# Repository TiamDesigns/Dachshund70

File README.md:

# Dachshund70

A tri-mode 60% keyboard I'm designing from scratch: the PCBs, the switch plate, the firmware, the config protocol, the driver and the configurator app. It runs over USB, Bluetooth LE and its own 2.4 GHz dongle, all on the nRF52840.

It was called the Dachshund60F until November 2026; older notes, PRs and the 26 October project review still use that name.

No boards have been made yet. All three PCBs are designed and the firmware is built and tested on a PC, so the next step is ordering them and bringing them up.

## Why I'm building this

I'm using this project to do two things at once:

1. **Explore hardware design with AI.** I want to see how far I can push an AI-assisted workflow on a real product: schematics, PCB layout, firmware, tooling and docs. I make the decisions and review everything, and Claude Code does a lot of the legwork. This repo is the record of how that went.
2. **Learn high-speed peripherals properly.** A keyboard looks simple, but doing it right covers USB device design, Bluetooth LE, a proprietary 2.4 GHz radio link, SPI and I2C displays, addressable LEDs, flash storage and power management. I want to understand each one well enough to design it, not just copy it.

And at the end of it I want a keyboard I actually enjoy using every day.

## Project goals

### Hardware

- Design all the boards myself in KiCad: the mainboard, a USB-C daughterboard and the dongle, plus an FR4 switch plate.
- Use a pre-certified nRF52840 module (Raytac MDBT50Q-P1MV2) and get the antenna keep-out, power and USB right the first time.
- Make it nice to type on: hot-swap switches, screw-in stabilisers, a gasket-mounted plate, and a horizontal roller encoder that turns like a mouse wheel.
- Run from USB or a single LiPo cell, with proper charging and a power path so it still works with the battery switched off.
- Measure everything when the boards arrive: rails, current draw in every state, scan rate, latency and radio range. The plan is in [docs/bringup-test-plan.md](docs/bringup-test-plan.md).

### Firmware

- Write my own firmware on Zephyr / nRF Connect SDK, not a fork of QMK or ZMK.
- Keep the keymap logic in plain C with no hardware in it, so it runs as unit tests on a PC.
- Be a complete USB keyboard: NKRO with boot-protocol fallback for BIOS and KVMs, media keys, lock LEDs, and suspend and remote wakeup.
- Support the advanced stuff: tap-hold, combos, tap dance, macros, key overrides, Caps Word, Auto Shift, Leader, mouse keys and the encoder.
- Never crash or corrupt flash on a bad packet. Every index and length from the host is checked, and the parser is fuzzed.

### Wireless

- Bluetooth LE HID with several host profiles and a switch key.
- A 2.4 GHz dongle on a second nRF52840 with low latency, polling at 1000 Hz (the limit for full-speed USB).
- Battery reporting, idle sleep and wake on key press.

### Driver and app

- No kernel driver. The board shows up as a normal HID keyboard plus one vendor-defined HID interface for configuration, so it works anywhere with nothing to install.
- A TypeScript host library (the "driver") that talks to that interface over WebHID in the browser or node-hid on the desktop.
- **Doghouse**, the configurator: keymap editing, advanced keys, macros, settings and firmware updates. It runs in Chrome or Edge, or as a desktop app for Windows, macOS and Linux that updates itself. It's in warm earth tones and dog-themed, because the boards are named after dogs.

### Doing it properly

- One protocol definition (`protocol/protocol.yaml`), with the C and TypeScript code generated from it.
- Versioned, CRC-checked, wear-levelled settings in flash, with migrations.
- CI that runs the unit tests, the host-library tests, the app build, protocol fuzzing, and debug and release firmware builds on every PR.
- Write down what changed and what's been tested in [PROGRESS.md](PROGRESS.md).

## The board

| | |
| --- | --- |
| MCU | nRF52840 (Raytac MDBT50Q-P1MV2 module) |
| Layout | 60% with an F-row, 80 switch positions, split or 6.25u spacebar |
| Matrix | 6 × 15, COL2ROW, diodes on every switch |
| Switches | Kailh hot-swap sockets (3 soldered positions on the spacebar row) |
| Encoder | Bourns PEC12R-2230F-S0024: shaft parallel to the board, 24 detents, push switch, 30 mm shaft, used as a 2u roller. On its own module board, cabled to the mainboard |
| Lighting | 6 × SK6812MINI-E indicators: layer, a 4-step battery gauge, and Caps Lock. No per-key RGB |
| Display | Sharp LS027B7DH01 2.7" memory LCD (240 × 400 on end), plugged into the mainboard's J4 with its 5 V boost on board; OLED and e-paper overlays still build for wired adapters |
| Power | USB-C on a daughterboard, 1S LiPo on JST-PH, MCP73831 charger with a load-sharing power path |
| Connectivity | USB, Bluetooth LE, 2.4 GHz dongle |
| Bootloader | Adafruit nRF52 UF2 bootloader: double-tap reset and drag a `.uf2` onto the drive |
| USB IDs | pid.codes test PIDs 1209:0001 (keyboard), 1209:0002 (dongle), 1209:0003 (bootloader) |

## Where it's at

The firmware follows the build order in [SPEC.md](SPEC.md): wired first, then wireless.

| Phase | What it covers | Status |
| --- | --- | --- |
| 1 | Scaffold: monorepo, CI, Zephyr app | Done |
| 2 | Board bring-up, USB enumeration, UF2 bootloader | Done |
| 3 | Matrix scan, debounce, keycodes, layers, tap-hold | Done |
| 4 | Full USB HID: NKRO, media keys, lock LEDs, sleep and wake | Done |
| 5 | Config protocol v1 over a vendor HID interface | Done |
| 6 | Saving settings to flash | Done |
| 7 | Host library (WebHID and node-hid) | Done |
| 8 | Doghouse on real boards | Done |
| 9 | Advanced keys, macros and the encoder | Done |
| 10 | Indicator colours and global settings | Done |
| 11 | In-app firmware updates | Done |
| 12 | Bluetooth LE | Done |
| 13 | Power management, battery and input delay | Done |
| 14 | 2.4 GHz dongle firmware | Done |
| 15 | Desktop app packaging and auto-update | Done |

"Done" means built and tested on a PC and in CI. None of it has run on a real board yet, because there isn't one.

## Repo layout

| Folder | What's in it |
| --- | --- |
| `hardware/` | KiCad 10 projects: mainboard, USB-C daughterboard, dongle and plate, STEP exports, and the case (`hardware/case/`, CadQuery) |
| `boards/Dachshund70/` | Pin map, keyboard definition, Zephyr board files and the UF2 bootloader board |
| `boards/Pup/` | A one-key test board: the keyboard firmware on Nordic's nRF52840 Dongle, for trying the wireless outputs before the PCB exists |
| `firmware/` | The keyboard firmware. `firmware/core/` is the hardware-free keymap engine and its tests |
| `dongle/` | 2.4 GHz receiver firmware (see `dongle/README.md` to flash and pair it) |
| `protocol/` | `protocol.yaml` and the code generator |
| `host-lib/` | The TypeScript host library, mock board and tests |
| `app/` | Doghouse, the configurator (Svelte 5 + Vite), and its desktop app in `app/src-tauri/` (Tauri) |
| `docs/` | Bring-up and test plan, and my design decisions |

## Trying it out

You don't need a board to play with most of it.

**Doghouse with demo boards**

```sh
cd app
npm install
npm run dev
```

Then open http://localhost:5173/?demo. To use a real board, open http://localhost:5173 in Chrome or Edge and click **Connect a board…**.

**Tests**

```sh
# keymap engine and protocol (C, runs on the PC)
cmake -S firmware/core -B firmware/core/build
cmake --build firmware/core/build
ctest --test-dir firmware/core/build --output-on-failure

# host library
cd host-lib && npm ci && npm test
```

**Firmware**

From an nRF Connect SDK v3.4.1 shell, in the repo root:

```sh
west build -p -b dachshund70/nrf52840 -d build/firmware firmware -- -DBOARD_ROOT="$PWD"
```

[CLAUDE.md](CLAUDE.md) has every command, including release builds, display panels, the bootloader and flashing.

## Docs

- [SPEC.md](SPEC.md): scope and build order
- [PROGRESS.md](PROGRESS.md): what's done, what's tested, known issues
- [docs/design-decisions.md](docs/design-decisions.md): the decisions I made along the way and what I've learnt
- [docs/bringup-test-plan.md](docs/bringup-test-plan.md): how each board gets flashed, tested and measured
- [protocol/README.md](protocol/README.md): the config protocol
- [SCHEDULED_TASKS.md](SCHEDULED_TASKS.md): open tasks

## Licence and disclaimer

This is open source and open hardware. You're free to copy it, change it, build it and sell it.

- **Code** (firmware, host library, Doghouse, protocol, scripts) is under the [MIT License](LICENSE).
- **Hardware** (everything in `hardware/`: the three PCBs and the plate) is under the [CERN Open Hardware Licence v2, Permissive](hardware/LICENSE) (CERN-OHL-P-2.0).
- **Third-party files** keep their own licences. The keyswitch footprints and 3D models are CC-BY-SA-4.0 (see `hardware/Dachshund70/lib/README.md`), and the bootloader build fetches Adafruit's MIT-licensed source.

Both licences are permissive. You can make your own boards, fork the firmware, put it in a product, or sell keyboards based on it, commercially or not. All I ask, and all the licences require, is that you keep the copyright and licence notices with what you copy.

Please read this before you build one:

- **No warranty.** This is a personal learning project, provided as is. At the time of writing no board has been manufactured or tested, so the designs may have mistakes. Check them yourself before ordering.
- **Lithium batteries can be dangerous.** The board charges a LiPo cell. Use a cell with its own protection circuit, check the connector polarity (JST-PH polarity isn't standard between vendors), and don't leave it charging unattended until you've tested your build.
- **USB IDs: change them before you give a board to anyone.** I've chosen not to register USB IDs for this project, because my board only lives on my desk. The firmware uses pid.codes *test* PIDs (1209:0001, 0002 and 0003), which anyone may use for in-house testing but which **must not** be used on a device that's given away, sold or manufactured. Every board using them looks identical to the OS, and to every other project that uses the same test IDs. If your boards will leave your hands, get your own VID/PID (a free PID from [pid.codes](https://pid.codes/howto/) for open-source hardware, or a VID from the USB-IF) and change them in `firmware/Kconfig`, the dongle and bootloader configs, and `boards/Dachshund70/board.json`.
- **Certification.** The radio module is pre-certified, but a finished product may still need its own testing (FCC, CE and so on) before you sell it. That's on you.

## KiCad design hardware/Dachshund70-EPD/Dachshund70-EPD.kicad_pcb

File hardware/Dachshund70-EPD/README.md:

# Dachshund70 e-paper adapter

Rev 1.5 (2026-11-25), checked against Good Display's GDEY027T91-FT11 specification (rev 1.0, 2024-11-06). Joins the wired mainboard's screen connector (`hardware/Dachshund70-Wired/`, J4) to Good
Display's [GDEY027T91-FT11](https://www.good-display.com/product/611.html): a 2.7" e-paper (SSD1680, 264 × 176,
70.42 × 45.8 × 2.1 mm, picture 57.29 × 38.19 mm) with an FT6336U capacitive touch panel and a 4-LED front light. It
fits the right-hand column between the knob and the arrow keys with the picture as wide as the knob. (Rev 1.0 was
for the 3.7" GDEY037T03-FT21, rev 1.1 for the 2.9" GDEY029T94-FT01; both were too big for the case.) The panel comes
bare on three FPCs, so this board carries the e-paper's booster circuit and the front light's driver. KiCad 10,
2 layers, 44 × 30 mm (narrower than the panel, to sit behind it), every part on the top. ERC 0; DRC clean
(0 violations, 0 unconnected, schematic parity clean). Not ordered, not tested.

## Connectors

J2 (e-paper), J3 (touch) and J4 (front light) are Hirose FH34SRJ dual-contact sockets (contacts top and bottom, 1 mm
high, LCSC C324726 / C224194), so a panel tail works either way up after it folds under the panel. Their footprints
are in `lib/Dachshund70-EPD.pretty` (made from LCSC's land patterns by `tools/mk_fh34.py`). They face the top edge
(y = 100): J4 (front light) at x 105.4, J2 (e-paper) at 122, J3 (touch) at 138.6. In the case the board sits under
the panel, component side up, turned 180° from this view; the case model was used to set each socket's pin order so
that each folded tail's pin 1 lands on the panel's pin 1. So J2 and J3 are numbered in reverse of the panel (socket
pin k = panel pin 25 − k, and 7 − k); J4 matches the panel. J1 (to the mainboard) is a bottom-contact Hirose FH12-16S
facing the bottom edge (y = 130) at x 122.

| Ref | To | Pins |
|---|---|---|
| J1 | mainboard J4, FH12-16S (16-way 0.5 mm FFC) | 1-2 +3V3, 3 GND, 4 TP_RST, 5 GND, 6 TP_INT, 7 TP_SCL, 8 TP_SDA, 9 FL_PWM, 10 not used (TP_EN), 11 EPD_BUSY, 12 EPD_RST, 13 EPD_DC, 14 EPD_MOSI, 15 EPD_SCK, 16 EPD_CS |
| J2 | e-paper FPC, FH34SRJ-24S | panel pins (socket pin = 25 − panel pin), per the spec (SSD1680): 2 GDR, 3 RESE, 5 VSH2, 8 BS1 (to GND: 4-wire SPI), 9 BUSY, 10 RES#, 11 D/C#, 12 CS#, 13 SCL, 14 SDA, 15 VDDIO, 16 VCI, 17 VSS, 18 VDD, 20 VSH1, 21 VGH, 22 VSL, 23 VGL, 24 VCOM; 1, 4, 6, 7 (TSCL/TSDA, no external sensor) and 19 (VPP, for test) not connected |
| J3 | touch FPC, FH34SRJ-6S | panel pins (socket pin = 7 − panel pin), per the spec: 1 GND, 2 INT, 3 RST, 4 VDD (+3V3), 5 SCL, 6 SDA (pull-ups are on the mainboard) |
| J4 | front-light FPC, FH34SRJ-6S | per the spec: 1-2 A(+) (FL_VOUT), 3-4 NC, 5-6 K(-) (FL_FB) |

## Circuits

- **E-paper booster**, as the spec's reference circuit: L1 47 µH (3015, 430 mA), Q1 Si1308EDL switched by GDR (R4 1M
  pull-down) with R1 2.2 Ω current sense on RESE, D3 to VGH, and the C10 (4.7 µF 25 V) / D1 / D2 charge pump to VGL
  (MBR0530 Schottkys), with 1 µF (50 V) on VSH2, VDD, VSH1, VGH, VSL, VGL, VCOM and VCI/VDDIO, and C11 4.7 µF on the
  3.3 V input.
- **Front light**: the FT11's four LEDs are in series (up to 12 V, 15 mA), so U1 (TPS61040, LCSC C7722) boosts 3.3 V
  and regulates their current: L2 10 µH, D4 MBR0530, C13 1 µF 50 V on the output, R2 82 Ω from the LEDs' cathode to
  ground (1.233 V / 82 Ω = 15 mA). FL_PWM (GPIO40) drives the TPS61040's EN to dim it with PWM (keep it under about
  1 kHz); R3 (100k) holds it off at reset.
- **Touch**: straight through, with C12 (100 nF) at J3.

## Layout

Two layers with ground pours on both, every ground pad joined solid (`Dachshund70-EPD.kicad_dru`), and one via per
cut-off pour area. Routed with the mainboard's grid router (`tools/`: placement in `epd_place.json`, net order in
`plan.json`, `epost.sh` for prune, pour, stitch and DRC).

## Open checks

- **Front-light open circuit.** The TPS61040 has no over-voltage limit: with the LEDs unplugged its output can rise
  to the switch's 28 V rating. C13 is 50 V; don't run the light without the panel attached.
- **FPC tails.** The case model sets the sockets' pin order and sides; the 6-pin tails' exact positions in Good
  Display's drawing are approximate, so check the fit on the first panel.
- **FPC tail lengths.** The 24-pin tail is 12.5 mm wide and about 30 mm long, the touch tail about 36 mm, both leaving the
  panel's bottom end; check they reach J2 and J3 when folded behind the panel in the case model.
- **FFC to the mainboard.** 16-way, 0.5 mm, 60 mm, opposite-side contacts (type B), for the case's two-fold route
  (pin 1 meets pin 1).
- **Mounting.** No holes: the case decides how the board and panel are held.

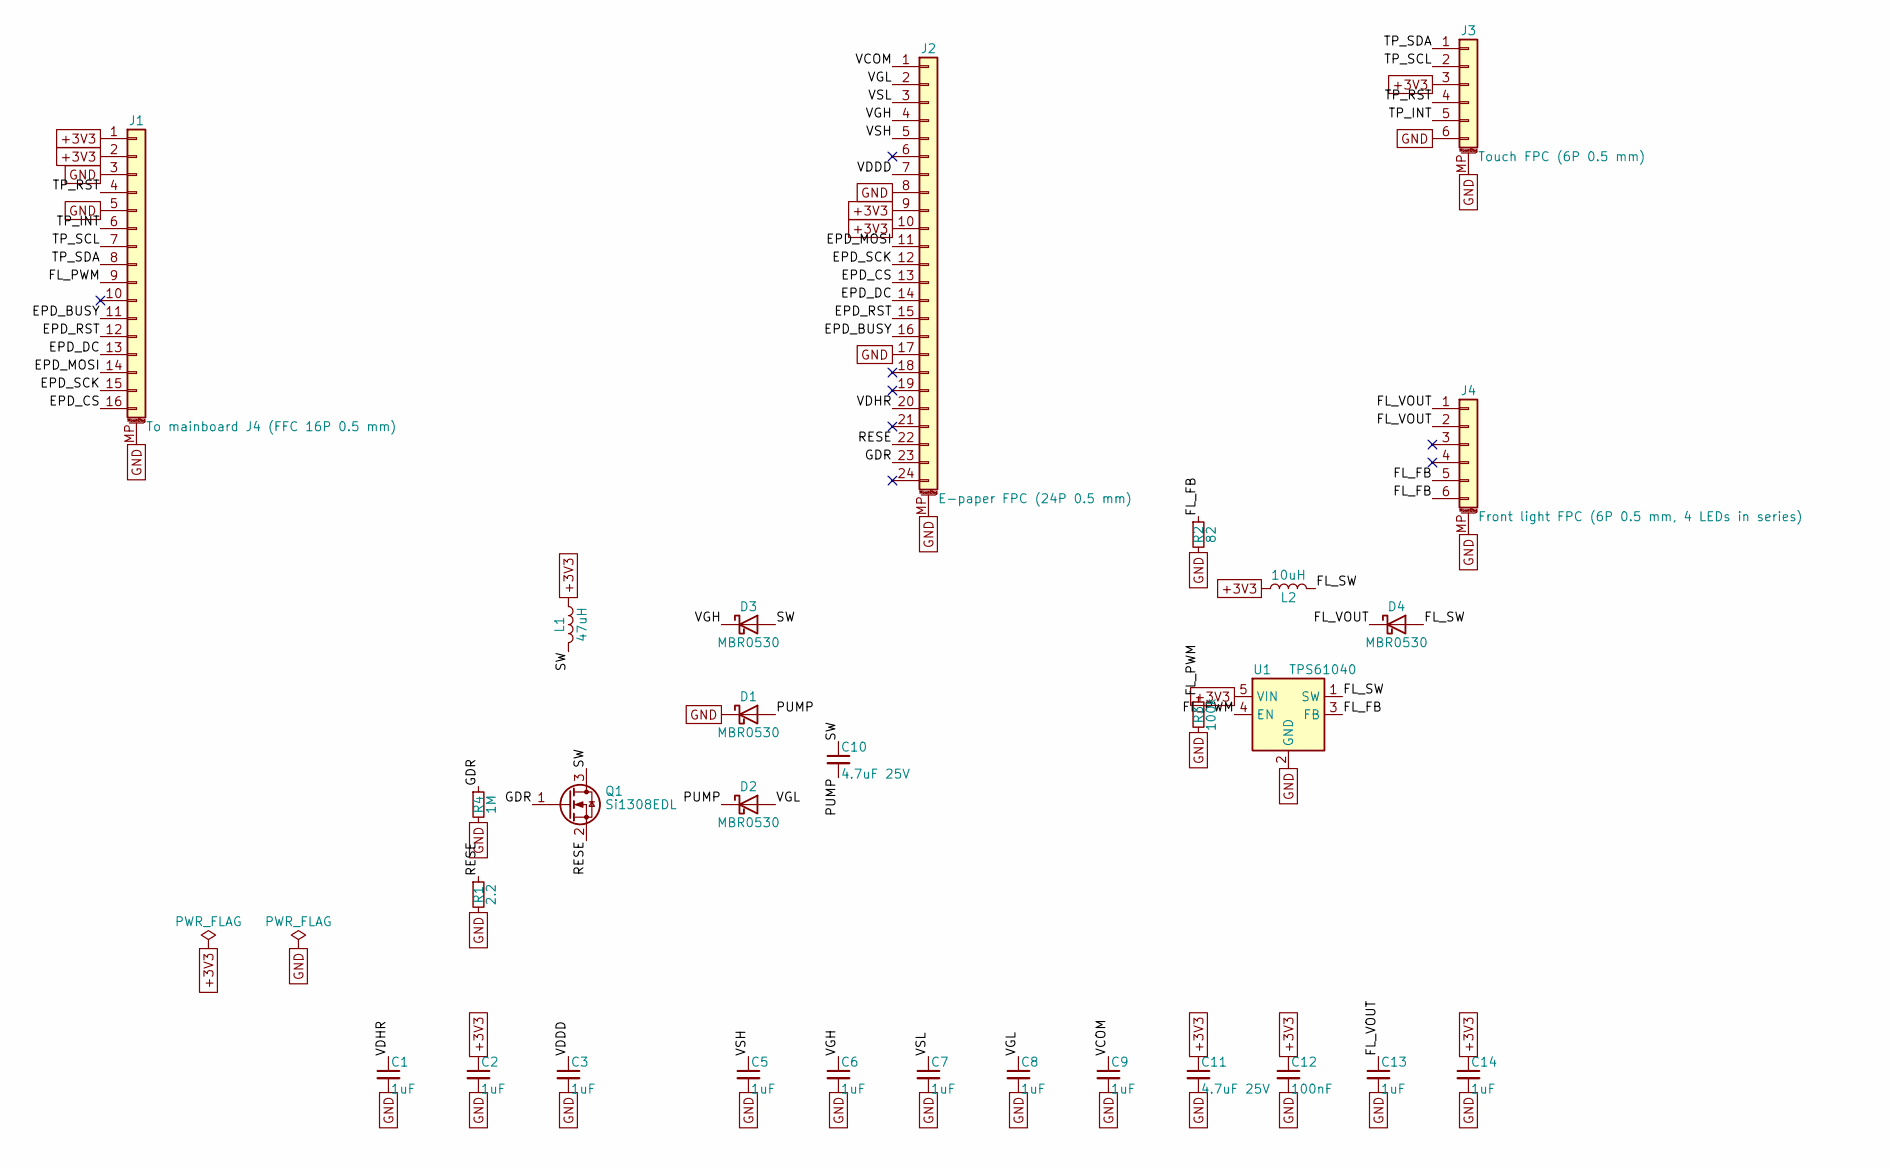
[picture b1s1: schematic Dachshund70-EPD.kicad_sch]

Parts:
C1, C2, C3, C5, C6, C7, C8, C9, C13, C14: 1uF; C_0603_1608Metric; MPN CL10A105KB8NNNC; LCSC C15849
C10, C11: 4.7uF 25V; C_0805_2012Metric; MPN CL21A475KAQNNNE; LCSC C1779
C12: 100nF; C_0603_1608Metric; MPN CC0603KRX7R9BB104; LCSC C14663
D1, D2, D3, D4: MBR0530; D_SOD-123; MPN MBR0530T1G; LCSC C82046
J1: To mainboard J4 (FFC 16P 0.5 mm); Hirose_FH12-16S-0.5SH_1x16-1MP_P0.50mm_Horizontal; MPN Hirose FH12-16S-0.5SH(55); LCSC C596731
J2: E-paper FPC (24P 0.5 mm); Hirose_FH34SRJ-24S-0.5SH_1x24-1MP_P0.50mm_Horizontal; MPN Hirose FH34SRJ-24S-0.5SH(50) (dual cont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; LCSC C324726
J3: Touch FPC (6P 0.5 mm); Hirose_FH34SRJ-6S-0.5SH_1x06-1MP_P0.50mm_Horizontal; MPN Hirose FH34SRJ-6S-0.5SH(50) (dual conta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; LCSC C224194
J4: Front light FPC (6P 0.5 mm, 4 LEDs in series); Hirose_FH34SRJ-6S-0.5SH_1x06-1MP_P0.50mm_Horizontal; MPN Hirose FH34SRJ-6S-0.5SH(50) (dual conta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; LCSC C224194
L1: 47uH; L_Changjiang_FNR3015S; MPN FNR3015S470MT (47uH 430mA, 3015); LCSC C167766
L2: 10uH; L_1008_2520Metric; MPN FHD252012S-100MT (10uH 1A, 2520); LCSC C602018
Q1: Si1308EDL; SOT-323_SC-70; MPN SI1308EDL-T1-GE3; LCSC C469327
R1: 2.2; R_0603_1608Metric; MPN 0603WAF220KT5E; LCSC C22939
R2: 82; R_0603_1608Metric; MPN 0603WAF820JT5E; LCSC C23255
R3: 100k; R_0603_1608Metric; MPN 0603WAF1003T5E; LCSC C25803
R4: 1M; R_0603_1608Metric; MPN 0603WAF1004T5E; LCSC C22935
U1: TPS61040; SOT-23-5; MPN TPS61040DBVR; LCSC C7722

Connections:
+3V3: C2.1, C11.1, C12.1, C14.1, J1.1, J1.2, J2.9, J2.10, J3.3, L1.1, L2.1, U1.5 (VIN)
/EPD_BUSY: J1.11, J2.16
/EPD_CS: J1.16, J2.13
/EPD_DC: J1.13, J2.14
/EPD_MOSI: J1.14, J2.11
/EPD_RST: J1.12, J2.15
/EPD_SCK: J1.15, J2.12
/FL_FB: J4.5, J4.6, R2.1, U1.3 (FB)
/FL_PWM: J1.9, R3.1, U1.4 (EN)
/FL_SW: D4.2 (A), L2.2, U1.1 (SW)
/FL_VOUT: C13.1, D4.1 (K), J4.1, J4.2
/GDR: J2.23, Q1.1 (G), R4.1
/PUMP: C10.2, D1.2 (A), D2.1 (K)
/RESE: J2.22, Q1.2 (S), R1.1
/SW: C10.1, D3.2 (A), L1.2, Q1.3 (D)
/TP_INT: J1.6, J3.5
/TP_RST: J1.4, J3.4
/TP_SCL: J1.7, J3.2
/TP_SDA: J1.8, J3.1
/VCOM: C9.1, J2.1
/VDDD: C3.1, J2.7
/VDHR: C1.1, J2.20
/VGH: C6.1, D3.1 (K), J2.4
/VGL: C8.1, D2.2 (A), J2.2
/VSH: C5.1, J2.5
/VSL: C7.1, J2.3
GND: C1.2, C2.2, C3.2, C5.2, C6.2, C7.2, C8.2, C9.2, C11.2, C12.2, C13.2, C14.2, D1.1 (K), J1.3, J1.5, J1.MP (MountPin), J2.8, J2.17, J2.MP (MountPin), J3.6, J3.MP (MountPin), J4.MP (MountPin), R1.2, R2.2, R3.2, R4.2, U1.2 (GND)

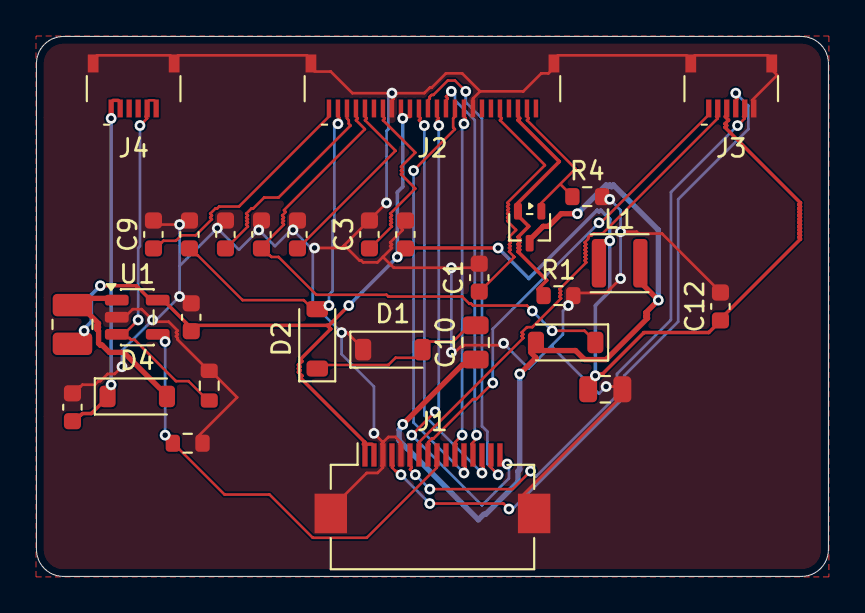
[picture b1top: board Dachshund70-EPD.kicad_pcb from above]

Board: 2 copper layers, 44.0 x 30.0 mm, 29 parts (0 on the bottom side), 27 nets.
